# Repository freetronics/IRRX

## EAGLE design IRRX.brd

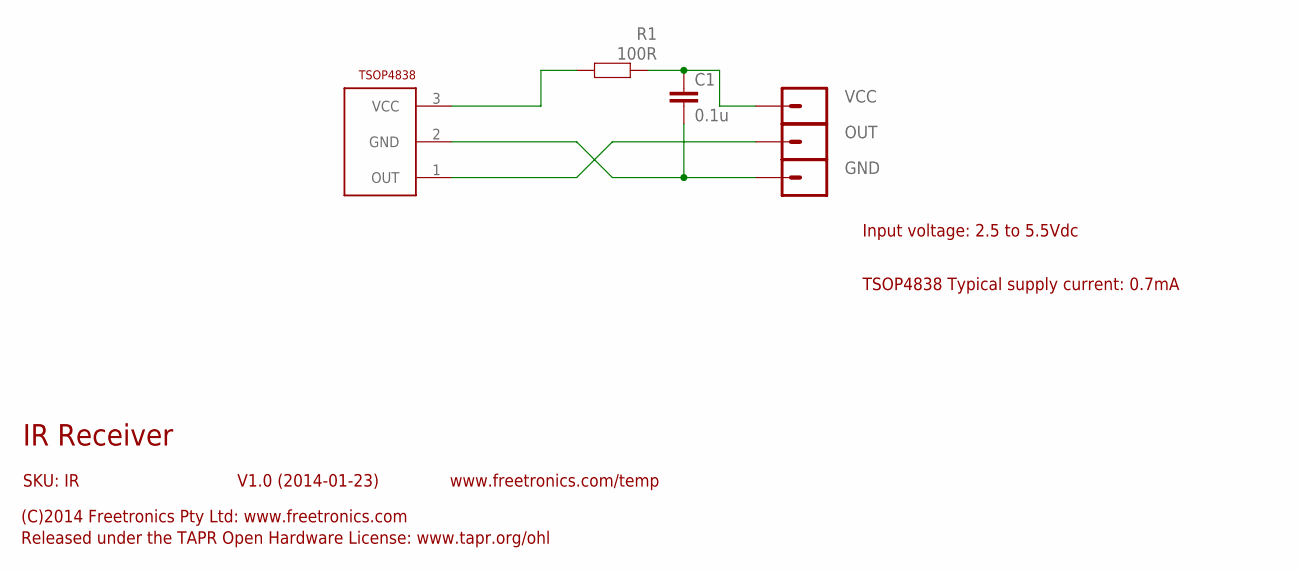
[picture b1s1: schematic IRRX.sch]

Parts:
C1: 0.1u; 0603
GND: M01PTH; 1X01
OUT: M01PTH; 1X01
R1: 100R; 0603
TSOP4838: TSOP4838; TO220
VCC: M01PTH; 1X01

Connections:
GND: C1.2, GND.1, TSOP4838.2 (GND)
unnamed: OUT.1, TSOP4838.1 (OUT)
unnamed: R1.2, TSOP4838.3 (VCC)
unnamed: C1.1, R1.1, VCC.1

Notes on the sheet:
IR Receiver
V1.0 (2014-01-23)
SKU: IR
(C)2014 Freetronics Pty Ltd: www.freetronics.com
Released under the TAPR Open Hardware License: www.tapr.org/ohl
www.freetronics.com/temp
Input voltage: 2.5 to 5.5Vdc
TSOP4838 Typical supply current: 0.7mA

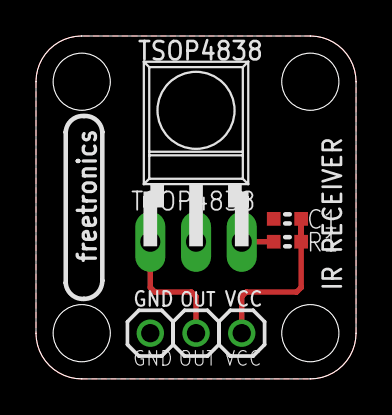
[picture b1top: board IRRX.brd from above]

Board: 2 copper layers, 17.8 x 19.1 mm, 6 parts (0 on the bottom side), 4 nets.

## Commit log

2014-01-23 v1.0 Initial Project

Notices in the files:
parts and their libraries:
freetronics-original: Licensing: CC v3.0 Share-Alike You are welcome to use this library for commercial purposes.
